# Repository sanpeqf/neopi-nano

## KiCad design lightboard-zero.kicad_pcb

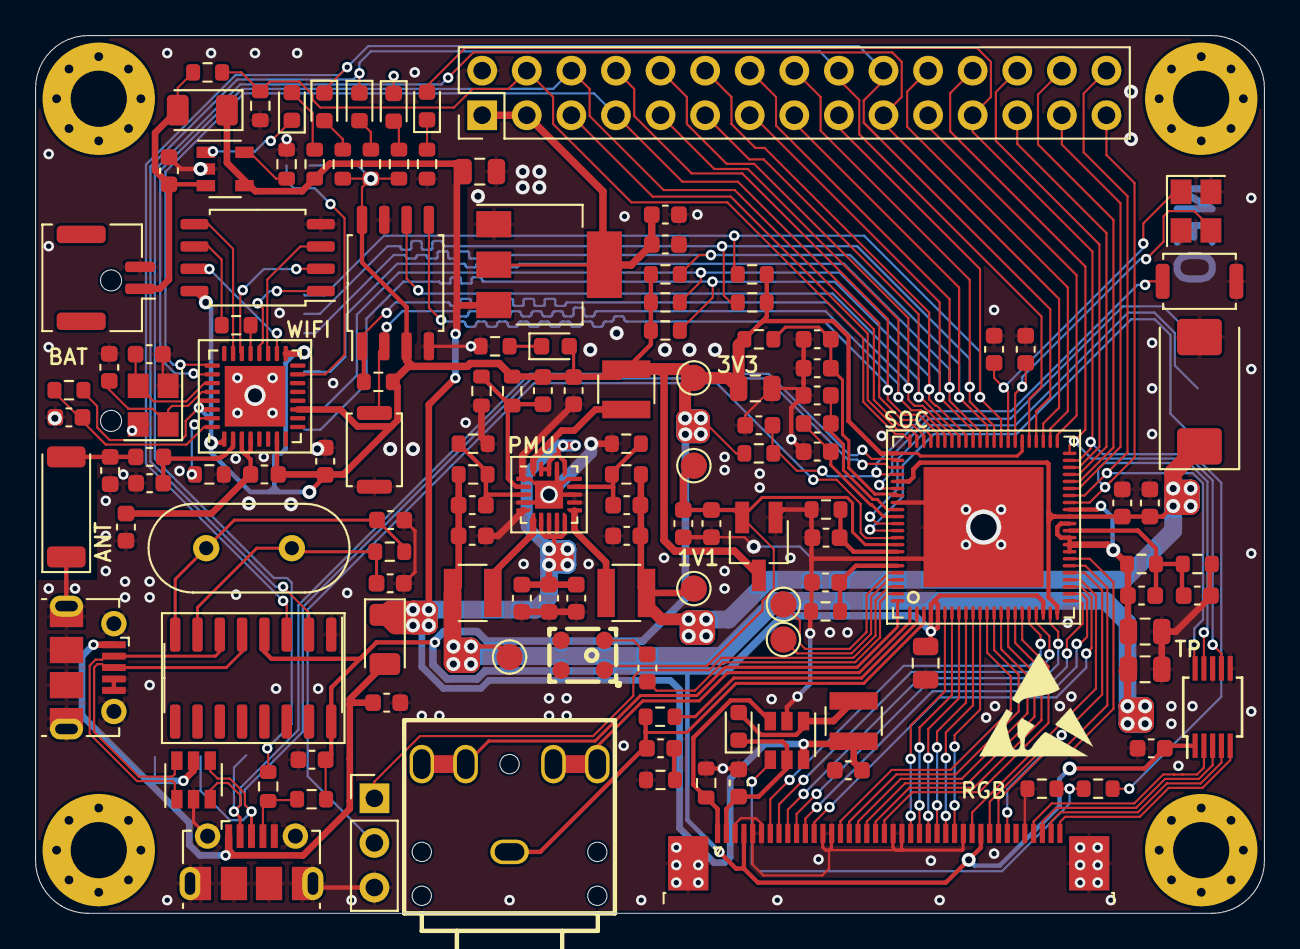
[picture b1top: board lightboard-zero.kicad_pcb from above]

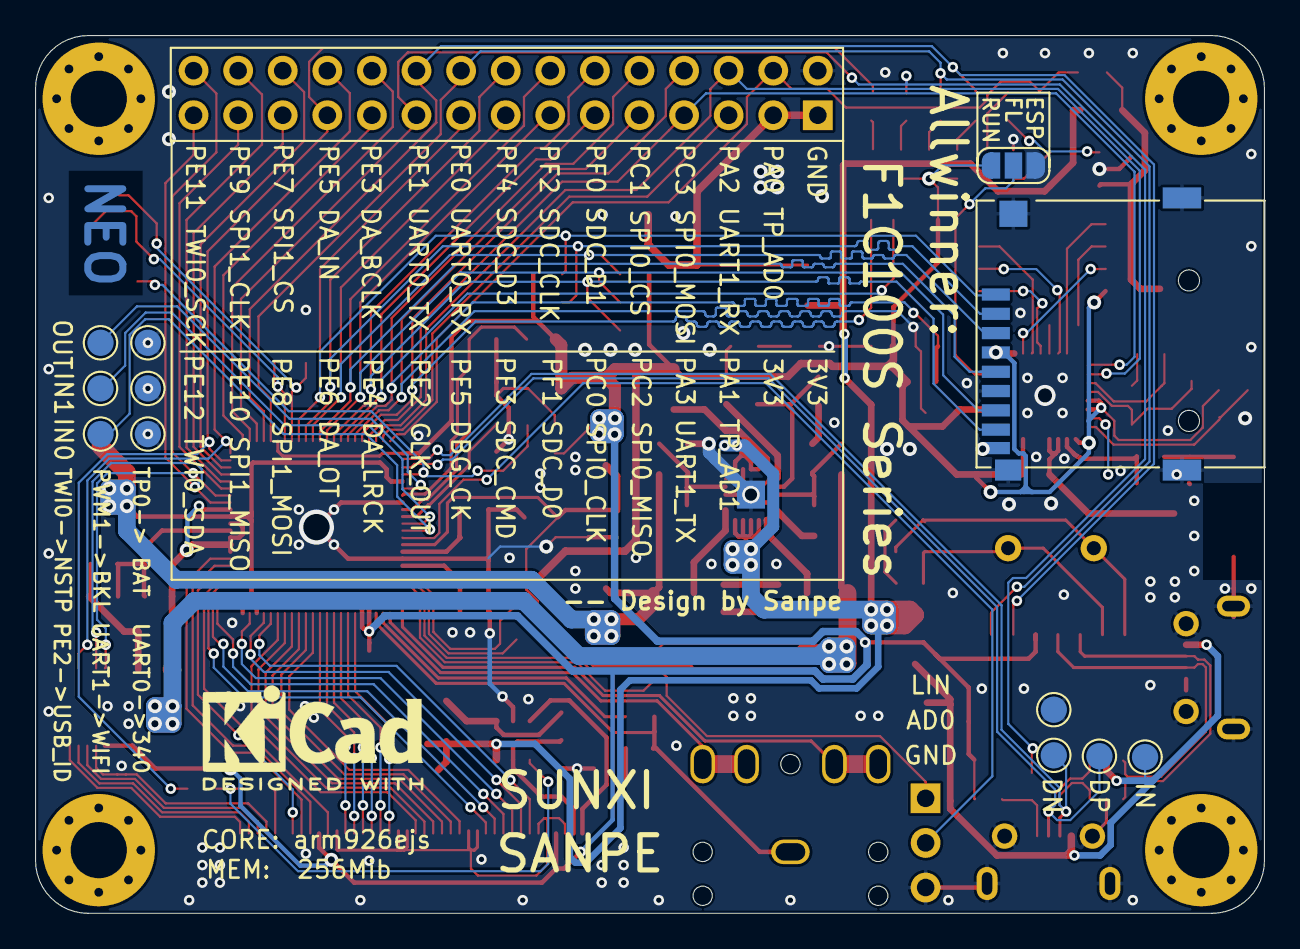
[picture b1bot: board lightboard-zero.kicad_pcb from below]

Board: 2 copper layers, 70.0 x 50.0 mm, 151 parts (12 on the bottom side), 125 nets.

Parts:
AE1: Antenna_Chip; Johanson_2450AT43F0100
C1, C9, C18, C22, C23, C34, C35, C37, C39, C47, C48, C49: 104; C_0603_1608Metric
C2, C6, C7, C8, C24, C27, C28, C43, C44: 18pF; C_0603_1608Metric
C3, C4, C5, C10, C12, C13, C14, C15, C16, C17, C19, C20, C21, C25, C26, C36, C38, C40, C45, C50, C51: 1uF; C_0603_1608Metric
C29: 330uF; CP_EIA-7343-15_Kemet-W
C30, C31, C32, C33, C46: 10uF; C_0805_2012Metric
C41, C42: 3pF; C_0603_1608Metric
CN1: PJ3F07-5P; AUDIO-TH_PJ3F07-5P
D1: D; LED_0603_1608Metric
D2, D3, D4, D5, D6, D8: LED; LED_0603_1608Metric
D7, D9: D; D_1206_3216Metric
H1, H2, H3, H4: MountingHole_Pad; MountingHole_3.2mm_M3_Pad_Via
J1, J2: USB_B_Micro; USB_Micro-B_Molex-105017-0001
J3: Conn_02x15_Odd_Even; PinHeader_2x15_P2.54mm_Vertical
J4: Conn_01x40_MountingPin; TE_4-1734839-0_1x40-1MP_P0.5mm_Horizontal
J5: Conn_01x03_Male; PinHeader_1x03_P2.54mm_Vertical
J6: Conn_01x02_Male; Molex_CLIK-Mate_502382-0270_1x02-1MP_P1.25mm_Vertical
JP1: Jumper_3_Bridged12; SolderJumper-3_P1.3mm_Open_RoundedPad1.0x1.5mm_NumberLabels
L1, L2, L3, L4: 2.2uH; L_Abracon_ASPI-3012S
L5, L6: 2.2nH; L_0603_1608Metric
MIC1: AOS3729A-T42-NXC; MIC-SMD_L3.8-W3.00-TL
R1, R12, R13, R17, R18, R20, R21, R22: 1K; R_0603_1608Metric
R2: R; R_0603_1608Metric
R3, R5, R6: 150K; R_0603_1608Metric
R4: 160K; R_0603_1608Metric
R7: 470K; R_0603_1608Metric
R8: 680K; R_0603_1608Metric
R9, R10: 200K; R_0603_1608Metric
R11, R29, R31, R38: 0R; R_0603_1608Metric
R14, R32, R34, R35, R36: 10K; R_0603_1608Metric
R15: 5R1; R_0603_1608Metric
R16: 1M; R_0603_1608Metric
R19, R23, R24, R25, R26, R27, R37: 47K; R_0603_1608Metric
R28: 22R; R_0603_1608Metric
R30: 200R; R_0603_1608Metric
R33: 12K; R_0603_1608Metric
SW1, SW2: SW_Push; SW_Push_SPST_NO_Alps_SKRK
TP1, TP2, TP3, TP4, TP5, TP6, TP7, TP8, TP9, TP10, TP11, TP12, TP13, TP14, TP15, TP16: TestPoint; TestPoint_Pad_D1.5mm
U1: XC6206; SC-59_Handsoldering
U2: EA3036; QFN-20-1EP_3x3mm_P0.45mm_EP1.6x1.6mm_ThermalVias
U3: tf; tf_lock
U4: W25Q128JVS; SOIC-8_5.23x5.23mm_P1.27mm
U5: f1c100s; QFN-88_EP_10x10_Pitch0.4mm
U6: PT4101; SOT-23-6
U7: CH340G; SOIC-16_3.9x9.9mm_P1.27mm
U8: SRV05-4; SOT-23-6
U9: AMS1117-3.3; SOT-223-3_TabPin2
U10: ESP8266EX; QFN-32-1EP_5x5mm_P0.5mm_EP3.45x3.45mm
U11: W25Q32JVSS; SOIC-8_5.23x5.23mm_P1.27mm
U12: TP4054_[C32574]; SOT-23-5
U13: ns2009; MSOP-10_3x3mm_P0.5mm
Y1: 24M; Crystal_SMD_Abracon_ABM8G-4Pin_3.2x2.5mm
Y2: 12M; Crystal_HC49-4H_Vertical
Y3: 48M; Crystal_SMD_Abracon_ABM8G-4Pin_3.2x2.5mm

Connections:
+5V: C12.2, C13.2, C14.2, C25.1, C46.1, D7.1 (K), D9.1 (K), L4.2, R1.1, U2.7 (VIN2), U2.8 (EN2), U2.9 (EN1), U2.10 (VIN1), U2.16 (VCC), U2.18 (EN3), U2.19 (VIN3), U6.6 (IN), U9.3 (VI), U12.4 (VCC)
AVCC: C9.1, C10.1, MIC1.1 (VDD), TP2.1, U1.2 (VOUT), U5.80 (AVCC)
BAT_ADC: J3.4, R34.2, R35.1, U5.66 (PA0)
CH340_USB_DN: J2.2 (D-), U7.6 (UD-), U8.1 (IO1)
CH340_USB_DP: J2.3 (D+), U7.5 (UD+), U8.6 (IO4)
CH340_XI: C27.1, R16.1, U7.7 (XI), Y2.1
CH340_XO: C28.1, R16.2, U7.8 (XO), Y2.2
CLK_OUT: D3.1 (K), J3.19, R38.1, U5.47 (PE2)
DA_BCLK: J3.22, U5.46 (PE3)
DA_LRCK: J3.21, U5.45 (PE4)
ESP8266_CLK: R30.1, U11.6 (CLK)
ESP8266_CMD: U10.20 (SDIO_CMD), U11.1 (~CS)
ESP8266_D0: U10.22 (SDIO_DATA_0), U11.2 (DO(IO1))
ESP8266_D1: U10.23 (SDIO_DATA_1), U11.5 (DI(IO0))
ESP8266_D2: U10.18 (SDIO_DATA_2), U11.7 (IO3)
ESP8266_D3: U10.19 (SDIO_DATA_3), U11.3 (IO2)
ESP8266_RST: C49.1, R36.2, U10.32 (~EXT_RSTB~)
ESP8266_XTALIN: C43.1, U10.28 (XTAL_IN), Y3.1
ESP8266_XTALOUT: C44.1, U10.27 (XTAL_OUT), Y3.3
FMINL: TP16.1, U5.84 (FMINL)
FMINR: TP15.1, U5.85 (FMINR)
HOSCI: C24.1, U5.51 (HOSCI), Y1.3
HOSCO: C2.1, U5.52 (HOSCO), Y1.1
HPCOM: C34.1, CN1.1 (A), R29.2, U5.3 (HPCOM)
HPCOMFB: R29.1, U5.2 (HPCOMFB)
HPL: CN1.4 (D), CN1.5 (E), U5.1 (HPL)
HPR: CN1.2 (B), CN1.3 (C), U5.88 (HPR)
HPVCC: C3.1, C8.1, C32.1, C33.1, C47.2, C48.1, C51.2, D2.2 (A), J4.4, J4.31, JP1.1 (A), L3.1, L6.2, R8.1, R11.2, R14.1, R18.1, R19.1, R21.1, R22.1, R23.1, R24.1, R25.1, R26.1, R27.1, R36.1, R37.1, TP1.1, U1.3 (VIN), U3.4 (VDD), U4.3 (IO2), U4.8 (VCC), U5.4 (HPVCC), U5.5 (VCC-IO), U5.20 (VCC-IO), U5.50 (VCC-IO), U5.67 (UVCC), U7.4 (V3), U7.16 (VCC), U10.1 (VDDA), U10.7 (CHIP_PU), U10.11 (VDDPST), U10.17 (VDDPST), U10.29 (VDDD), U10.30 (VDDA), U11.8 (VCC), U13.1 (VDD)
IO3V3: C35.1, C36.1, J3.1, J3.3, U9.2 (VO)
LCD_CLK: J4.30, U5.26 (PD18)
LCD_D2: J4.23, U5.6 (PD0)
LCD_D3: J4.24, U5.7 (PD1)
LCD_D4: J4.25, U5.8 (PD2)
LCD_D5: J4.26, U5.9 (PD3)
LCD_D6: J4.27, U5.10 (PD4)
LCD_D7: J4.28, U5.11 (PD5)
LCD_D10: J4.15, U5.12 (PD6)
LCD_D11: J4.16, U5.13 (PD7)
LCD_D12: J4.17, U5.14 (PD8)
LCD_D13: J4.18, U5.15 (PD9)
LCD_D14: J4.19, U5.16 (PD10)
LCD_D15: J4.20, U5.17 (PD11)
LCD_D18: J4.7, U5.18 (PD12)
LCD_D19: J4.8, U5.19 (PD13)
LCD_D20: J4.9, U5.21 (PD14)
LCD_D21: J4.10, U5.23 (PD15)
LCD_D22: J4.11, U5.24 (PD16)
LCD_D23: J4.12, U5.25 (PD17)
LCD_DE: J4.34, U5.27 (PD19)
LCD_HSYNC: J4.32, U5.28 (PD20)
LCD_VSYNC: J4.33, U5.29 (PD21)
LINL: J5.1, U5.86 (LINL)
LRADC: J5.2, U5.79 (LRADC0)
MICIN: C39.1, U5.87 (MICIN)
NOR_CS: J3.10, R14.2, U4.1 (~CS), U5.60 (PC1)
unnamed: AE1.2 (PCB_Trace), C41.1, L5.1
unnamed: C6.2, R3.1, R6.2, U2.14 (FB1)
unnamed: C7.2, R4.1, R7.2, U2.3 (FB2)
unnamed: C8.2, R5.1, R8.2, U2.2 (FB3)
unnamed: C34.2, R28.1
unnamed: C39.2, MIC1.4 (OUTPUT)
unnamed: C42.1, L5.2, U10.2 (LNA)
unnamed: C45.1, D9.2 (A), J6.1, R34.1, U12.3 (BAT)
unnamed: C50.2, L6.1, U10.3 (VDD3P3), U10.4 (VDD3P3)
unnamed: D1.2 (A), L4.1, U6.1 (SW)
unnamed: D2.1 (K), R17.1
unnamed: D3.2 (A), R18.2
unnamed: D4.1 (K), R20.1
unnamed: D5.2 (A), R21.2
unnamed: D6.2 (A), R22.2
unnamed: D8.1 (K), U12.1 (~GHRG)
unnamed: D8.2 (A), R1.2
unnamed: J1.4 (ID), R37.2, R38.2
unnamed: JP1.2 (C), U10.15 (GPIO0)
unnamed: L1.2, U2.11 (LX1)
unnamed: L2.2, U2.6 (LX2)
unnamed: L3.2, U2.20 (LX3)
unnamed: R2.2, U12.5 (PROG)
unnamed: R30.2, U10.21 (SDIO_CLK)
unnamed: R31.2, R32.1, U6.4 (EN)
unnamed: R33.1, U10.31 (RES12K)
PA1: J3.5, U5.65 (PA1)
PA2: J3.6, U5.64 (PA2), U10.26 (U0TXD)
PA3: J3.7, U5.63 (PA3), U10.25 (U0RXD)
PC0: J3.11, U4.6 (CLK), U5.59 (PC0)
PC2: J3.9, SW2.2, U4.2 (DO(IO1)), U5.61 (PC2)
PC3: J3.8, U4.5 (DI(IO0)), U5.62 (PC3)
PE0: D5.1 (K), J3.18, U5.49 (PE0)
PE1: D6.1 (K), J3.20, U5.48 (PE1)
PE5: J3.24, U5.44 (PE5), U13.7 (PENIRQ)
PE6: D4.2 (A), J3.23, R31.1, U5.43 (PE6)
PE7: J3.26, U5.42 (PE7)
PE8: J3.25, U5.41 (PE8)
PE9: J3.28, U5.40 (PE9)
PE10: J3.27, U5.39 (PE10)
PE11: J3.30, U5.38 (PE11), U13.10 (SCL)
PE12: J3.29, U5.37 (PE12), U13.9 (SDA)
PF0: J3.12, R23.2, U3.8 (DAT1), U5.58 (PF0)
PF1: J3.13, R24.2, U3.7 (DAT0), U5.57 (PF1)
PF2: J3.14, U3.5 (CLK), U5.56 (PF2)
PF3: J3.15, R25.2, U3.3 (CMD), U5.55 (PF3)
PF4: J3.16, R26.2, U3.2 (DAT3/CD), U5.54 (PF4)
PF5: J3.17, R27.2, U3.1 (DAT2), U5.53 (PF5)
RESET: C1.1, R19.2, SW1.2, U5.70 (RESET)
SOC_GND: AE1.1 (FEED), C1.2, C2.2, C3.2, C4.2, C5.2, C9.2, C10.2, C12.1, C13.1, C14.1, C15.1, C16.1, C17.1, C18.1, C20.1, C21.1, C23.2, C24.2, C25.2, C26.2, C27.2, C28.2, C29.2, C30.2, C31.2, C32.2, C33.2, C35.2, C36.2, C37.2, C38.2, C40.2, C41.2, C42.2, C43.2, C44.2, C45.2, C46.2, C47.1, C48.2, C49.2, C50.1, C51.1, J1.5 (GND), J1.6 (Shield), J2.4 (ID), J2.5 (GND), J2.6 (Shield), J3.2, J4.3, J4.5, J4.6, J4.13, J4.14, J4.21, J4.22, J4.29, J4.36, J4.MP (MountPin), J5.3, J6.2, JP1.3 (B), MIC1.2 (GND), MIC1.3 (GND), R2.1, R3.2, R4.2, R5.2, R9.1, R10.1, R13.2, R15.2, R17.2, R20.2, R28.2, R32.2, R33.2, R35.2, SW1.1, SW2.1, TP8.1, TP9.1, TP10.1, TP14.1, U1.1 (GND), U2.1 (GND3), U2.4 (GND2), U2.5 (GND2), U2.12 (GND1), U2.13 (GND1), U2.15 (AGND), U2.17 (AGND), U2.21 (EPAD), U3.6 (VSS), U3.9 (DET), U3.10 (SHIELD), U4.4 (GND), U4.7 (IO3), U5.74 (TVGND), U5.82 (AGND), U5.89 (EPAD), U6.2 (GND), U7.1 (GND), U8.2 (VN), U9.1 (GND), U10.33 (GND), U11.4 (GND), U12.2 (GND), U13.6 (GND), U13.8 (A0), Y1.2, Y1.4, Y3.2, Y3.4
SVREF: C22.2, C23.1, R12.2, R13.1, U5.33 (SVREF)
TPX1: J4.37, U13.2 (XP)
TPX2: J4.39, U13.4 (XN)
TPY1: J4.38, U13.3 (YP)
TPY2: J4.40, U13.5 (YN)
TV-IN0: TP5.1, U5.78 (TV-IN0)
TV-IN1: TP6.1, U5.77 (TV-IN1)
TV-VCC: C15.2, C18.2, R11.1, U5.73 (TV-VCC)
TV-VRN: C19.2, C20.2, U5.75 (TV-VRN)
TV-VRP: C19.1, C21.2, U5.76 (TV-VRP)
TVOUT: TP7.1, U5.72 (TVOUT)
USB-DN: J1.2 (D-), TP13.1, U5.68 (USB-DM), U8.3 (IO2)
USB-DP: J1.3 (D+), TP12.1, U5.69 (USB-DP), U8.4 (IO3)
USB_IN: C40.1, D7.2 (A), J1.1 (VBUS), J2.1 (VBUS), TP11.1, U8.5 (VP)
VCC-DRAM: C5.1, C7.1, C22.1, C30.1, C31.1, L2.1, R7.1, R12.1, TP3.1, U5.30 (VCC-DRAM), U5.31 (VCC-DRAM), U5.32 (VCC-DRAM), U5.34 (VCC-DRAM), U5.36 (VCC-DRAM)
VDD-CORE: C4.1, C6.1, C29.1, C37.1, C38.1, L1.1, R6.1, TP4.1, U5.22 (VDD-CORE), U5.35 (VDD-CORE), U5.71 (VDD-CORE)
VLED+: C26.1, D1.1 (K), J4.2, U6.5 (0V)
VLED-: J4.1, R15.1, U6.3 (FB)
VRA1: C16.2, R9.2, U5.81 (VRA1)
VRA2: C17.2, R10.2, U5.83 (VRA2)

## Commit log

2021-08-01 2021-8-1
